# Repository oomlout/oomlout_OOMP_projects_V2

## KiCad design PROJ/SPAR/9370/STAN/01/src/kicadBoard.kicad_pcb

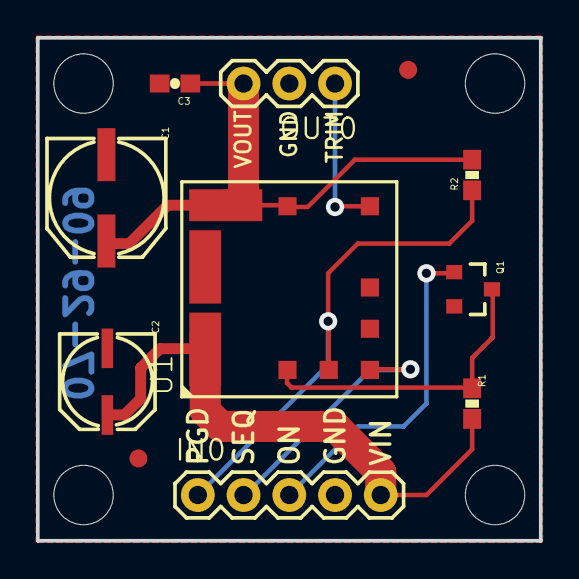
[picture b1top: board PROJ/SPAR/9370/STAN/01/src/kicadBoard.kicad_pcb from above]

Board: 16 copper layers, 27.9 x 27.9 mm, 16 parts (1 on the bottom side), 8 nets.

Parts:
C1: 100uF-25V; NIPPON_F80
C2: 22uF-35v; PANASONIC_C
C3: 0.1uF; 0603-CAP
FID1, FID2: FIDUCIAL1X2; FIDUCIAL-1X2
IN0: 1X05
OUT0: 1X03
Q1: MOSFET-NCHANNELSMD; SOT23-3
R1: 22K; 0603-RES
R2: 100K; 0603-RES
U1: DC-DC_CONVERTER
U$1, U$3, U$4, U$5: STAND-OFF
U$2: LOGO-SFENEW; SFE-NEW-WEBLOGO

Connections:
GND: C1.-, C2.-, C3.2, IN0.4, OUT0.2, Q1.2, U1.3, U1.7
unnamed: Q1.3, R1.1, U1.1
ON/OFF: IN0.3, Q1.1
PGOOD: IN0.1, R2.1, U1.10
SEQ: IN0.2, U1.9
TRIM: OUT0.1, U1.6
VIN: C2.+, IN0.5, R1.2, U1.2
VOUT: C1.+, C3.1, OUT0.3, R2.2, U1.4, U1.5

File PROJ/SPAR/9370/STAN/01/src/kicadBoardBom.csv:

"Id";"Designator";"Package";"Quantity";"Designation";"Supplier and ref";
1;"C3";"0603-CAP";1;"0.1uF";;;
2;"U$3,U$5,U$1,U$4";"STAND-OFF";4;"STAND-OFF";;;
3;"Q1";"SOT23-3";1;"MOSFET-NCHANNELSMD";;;
4;"FID2,FID1";"FIDUCIAL-1X2";2;"FIDUCIAL1X2";;;
5;"C1";"NIPPON_F80";1;"100uF-25V";;;
6;"R2";"0603-RES";1;"100K";;;
7;"C2";"PANASONIC_C";1;"22uF-35v";;;
8;"R1";"0603-RES";1;"22K";;;
9;"IN0";"1X05";1;"";;;
10;"U1";"DC-DC_CONVERTER";1;"DC-DC_CONVERTER";;;
11;"OUT0";"1X03";1;"";;;
12;"U$2";"SFE-NEW-WEBLOGO";1;"LOGO-SFENEW";;;

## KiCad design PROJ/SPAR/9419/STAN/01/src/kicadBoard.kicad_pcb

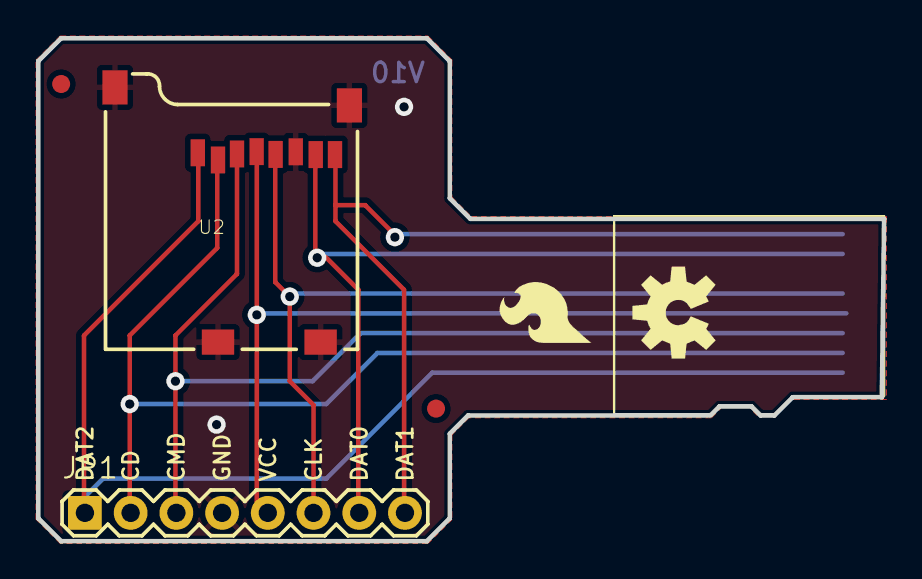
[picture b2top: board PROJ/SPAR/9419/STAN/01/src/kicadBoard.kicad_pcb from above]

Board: 16 copper layers, 47.0 x 27.9 mm, 9 parts (1 on the bottom side), 8 nets.

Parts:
FID1, FID2: FIDUCIAL1X2; FIDUCIAL-1X2
FRAME1: CREATIVE_COMMONS
JP1: 1X08
LOGO1: OSHW-LOGOM; OSHW-LOGO-M
LOGO2: SFE_LOGO_FLAME.2_INCH; SFE_LOGO_FLAME_.2
LOGO3: SFE_LOGO_NAME_FLAME.1_INCH; SFE_LOGO_NAME_FLAME_.1
U1: MICRO-SDCARD
U2: microSD Socket; MICROSD_1_1

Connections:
CD/DAT3: JP1.2, U1.CD/DAT3, U2.2
CLK: JP1.6, U1.CLK, U2.5
CMD: JP1.3, U1.CMD, U2.3
DAT0: JP1.7, U1.DAT0, U2.7
DAT1: JP1.8, U1.DAT1, U2.8
DAT2: JP1.1, U1.DAT2, U2.1
GND: JP1.4, U1.GND, U2.6, U2.CD1, U2.CD2, U2.GND1, U2.GND3
VCC: JP1.5, U1.VCC, U2.4

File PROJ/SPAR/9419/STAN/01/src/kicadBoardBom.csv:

"Id";"Designator";"Package";"Quantity";"Designation";"Supplier and ref";
1;"FID1,FID2";"FIDUCIAL-1X2";2;"FIDUCIAL1X2";;;
2;"U1";"MICRO-SDCARD";1;"MICRO-SDCARD";;;
3;"JP1";"1X08";1;"";;;
4;"LOGO1";"OSHW-LOGO-M";1;"OSHW-LOGOM";;;
5;"U2";"MICROSD_1_1";1;"microSD Socket";;;
6;"LOGO2";"SFE_LOGO_FLAME_.2";1;"SFE_LOGO_FLAME.2_INCH";;;
7;"FRAME1";"CREATIVE_COMMONS";1;"";;;
8;"LOGO3";"SFE_LOGO_NAME_FLAME_.1";1;"SFE_LOGO_NAME_FLAME.1_INCH";;;

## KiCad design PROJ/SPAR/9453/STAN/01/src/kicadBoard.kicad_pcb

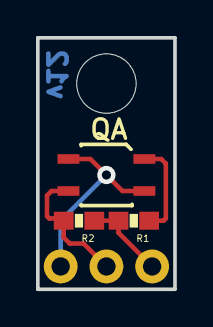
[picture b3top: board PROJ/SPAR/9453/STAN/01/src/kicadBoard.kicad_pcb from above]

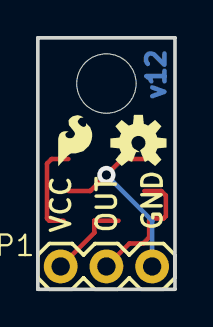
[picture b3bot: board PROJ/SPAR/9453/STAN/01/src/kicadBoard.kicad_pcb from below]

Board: 2 copper layers, 7.6 x 14.0 mm, 8 parts (3 on the bottom side), 4 nets.

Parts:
CC_TEXT1: CREATIVE_COMMONS
JP1: 1X03
JP2: LOGO-SFESK; SFE-LOGO-FLAME
JP3: STAND-OFF
R1: 100; 0603-RES
R2: 10K; 0603-RES
U1: QRE11131:1; QRE1113-1_1
U$1: OSHW-LOGOS; OSHW-LOGO-S

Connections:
GND: JP1.3, U1.2, U1.4
unnamed: R1.1, U1.1
OUT: JP1.2, R2.2, U1.3
VCC: JP1.1, R1.2, R2.1

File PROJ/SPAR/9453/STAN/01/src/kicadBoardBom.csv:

"Id";"Designator";"Package";"Quantity";"Designation";"Supplier and ref";
1;"U1";"QRE1113-1_1";1;"QRE11131:1";;;
2;"JP3";"STAND-OFF";1;"STAND-OFF";;;
3;"CC_TEXT1";"CREATIVE_COMMONS";1;"CREATIVE_COMMONS";;;
4;"R1";"0603-RES";1;"100";;;
5;"R2";"0603-RES";1;"10K";;;
6;"JP2";"SFE-LOGO-FLAME";1;"LOGO-SFESK";;;
7;"U$1";"OSHW-LOGO-S";1;"OSHW-LOGOS";;;
8;"JP1";"1X03";1;"";;;

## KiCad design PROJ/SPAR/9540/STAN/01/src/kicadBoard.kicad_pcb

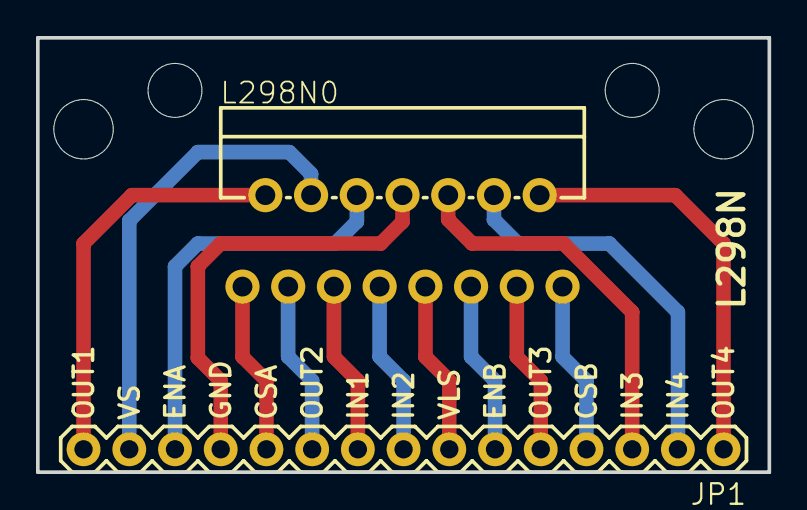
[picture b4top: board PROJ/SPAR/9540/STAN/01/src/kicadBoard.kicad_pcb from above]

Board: 2 copper layers, 40.6 x 24.1 mm, 5 parts (1 on the bottom side), 15 nets.

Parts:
JP1: M15; 1X15
JP2, JP3: STAND-OFF
JP4: LOGO-SFENEW; SFE-NEW-WEBLOGO
L298N0: L298HEATSINK; MULTIWATT15_6400BGHEATSINK

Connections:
CSA: JP1.11, L298N0.1
CSB: JP1.4, L298N0.15
ENA: JP1.13, L298N0.6
ENB: JP1.6, L298N0.11
GND: JP1.12, L298N0.8
IN1: JP1.9, L298N0.5
IN2: JP1.8, L298N0.7
IN3: JP1.3, L298N0.10
IN4: JP1.2, L298N0.12
OUT1: JP1.15, L298N0.2
OUT2: JP1.10, L298N0.3
OUT3: JP1.5, L298N0.13
OUT4: JP1.1, L298N0.14
VLS: JP1.7, L298N0.9
VS: JP1.14, L298N0.4

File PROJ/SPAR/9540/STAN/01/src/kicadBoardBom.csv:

"Id";"Designator";"Package";"Quantity";"Designation";"Supplier and ref";
1;"L298N0";"MULTIWATT15_6400BGHEATSINK";1;"L298HEATSINK";;;
2;"JP1";"1X15";1;"M15";;;
3;"JP2,JP3";"STAND-OFF";2;"STAND-OFF";;;
4;"JP4";"SFE-NEW-WEBLOGO";1;"LOGO-SFENEW";;;

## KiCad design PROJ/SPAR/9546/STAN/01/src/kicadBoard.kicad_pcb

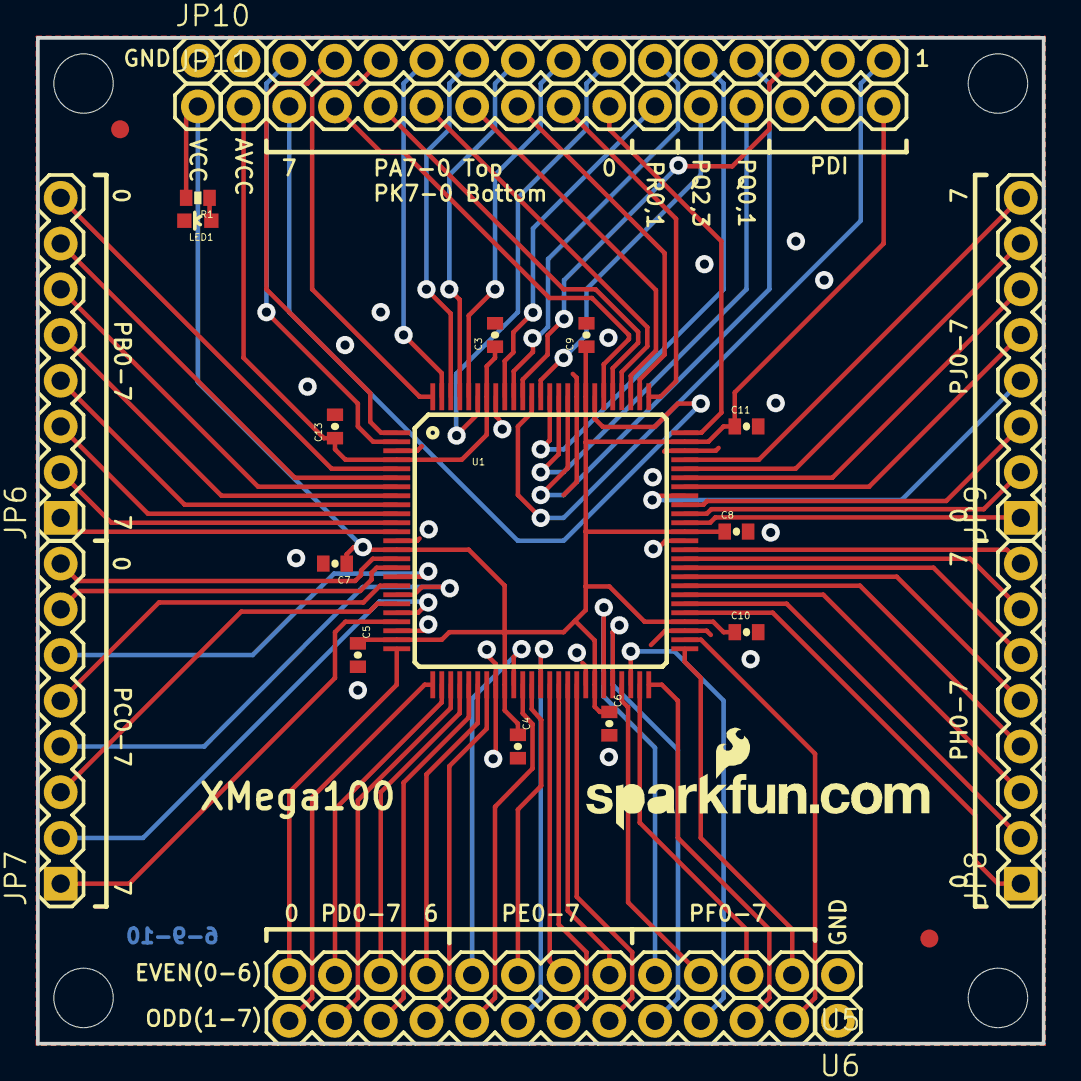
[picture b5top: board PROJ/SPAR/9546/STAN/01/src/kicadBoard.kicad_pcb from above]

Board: 2 copper layers, 55.9 x 55.9 mm, 28 parts (0 on the bottom side), 84 nets.

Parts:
C3, C4, C5, C6, C7, C8, C9, C10, C11, C13: 0.1uF; 0402-CAP
JP1: LOGO-SFENEW; SFE-NEW-WEBLOGO
JP2, JP3, JP4, JP5: STAND-OFF
JP6: Left Port B; 1X08
JP7: Left Port C; 1X08
JP8: Right Port H; 1X08
JP9: Right Port J; 1X08
JP10: TopEdge; 1X16
JP11: TopInside; 1X16
JP12, JP13: FIDUCIAL1X2; FIDUCIAL-1X2
LED1: Red; LED-0603
R1: 330; 0402-RES
U1: XMEGA-100SMD; TQFP-100-14X14MM
U5: BottonInside; 1X13
U6: BottomEdge; 1X13

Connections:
AVCC: C3.1, C13.1, JP11.2, U1.4, U1.94
GND: C3.2, C4.2, C5.2, C6.2, C7.2, C8.2, C9.2, C10.2, C11.2, C13.2, JP10.1, JP10.2, JP11.14, LED1.C, U1.3, U1.13, U1.23, U1.33, U1.43, U1.53, U1.63, U1.73, U1.84, U1.93, U5.1, U6.1
unnamed: LED1.A, R1.1
PA0: JP10.10, U1.95
PA1: JP10.9, U1.96
PA2: JP10.8, U1.97
PA3: JP10.7, U1.98
PA4: JP10.6, U1.99
PA5: JP10.5, U1.100
PA6: JP10.4, U1.1
PA7: JP10.3, U1.2
PB0: JP6.8, U1.5
PB1: JP6.7, U1.6
PB2: JP6.6, U1.7
PB3: JP6.5, U1.8
PB4: JP6.4, U1.9
PB5: JP6.3, U1.10
PB6: JP6.2, U1.11
PB7: JP6.1, U1.12
PC0: JP7.8, U1.15
PC1: JP7.7, U1.16
PC2: JP7.6, U1.17
PC3: JP7.5, U1.18
PC4: JP7.4, U1.19
PC5: JP7.3, U1.20
PC6: JP7.2, U1.21
PC7: JP7.1, U1.22
PD0: U1.25, U5.13
PD1: U1.26, U6.13
PD2: U1.27, U5.12
PD3: U1.28, U6.12
PD4: U1.29, U5.11
PD5: U1.30, U6.11
PD6: U1.31, U5.10
PD7: U1.32, U6.10
PDI_CLK: JP10.14, U1.90
PDI_DATA: JP10.16, U1.89
PE0: U1.35, U5.9
PE1: U1.36, U6.9
PE2: U1.37, U5.8
PE3: U1.38, U6.8
PE4: U1.39, U5.7
PE5: U1.40, U6.7
PE6: U1.41, U5.6
PE7: U1.42, U6.6
PF0: U1.45, U5.5
PF1: U1.46, U6.5
PF2: U1.47, U5.4
PF3: U1.48, U6.4
PF4: U1.49, U5.3
PF5: U1.50, U6.3
PF6: U1.51, U5.2
PF7: U1.52, U6.2
PH0: JP8.1, U1.55
PH1: JP8.2, U1.56
PH2: JP8.3, U1.57
PH3: JP8.4, U1.58
PH4: JP8.5, U1.59
PH5: JP8.6, U1.60
PH6: JP8.7, U1.61
PH7: JP8.8, U1.62
PJ0: JP9.1, U1.65
PJ1: JP9.2, U1.66
PJ2: JP9.3, U1.67
PJ3: JP9.4, U1.68
PJ4: JP9.5, U1.69
PJ5: JP9.6, U1.70
PJ6: JP9.7, U1.71
PJ7: JP9.8, U1.72
PK0: JP11.10, U1.75
PK1: JP11.9, U1.76
PK2: JP11.8, U1.77
PK3: JP11.7, U1.78
PK4: JP11.6, U1.79
PK5: JP11.5, U1.80
PK6: JP11.4, U1.81
PK7: JP11.3, U1.82
PQ0: JP10.13, U1.85
PQ1: JP11.13, U1.86
PQ2: JP10.12, U1.87
PQ3: JP11.12, U1.88
PR0: JP10.11, U1.91
PR1: JP11.11, U1.92
VCC: C4.1, C5.1, C6.1, C7.1, C8.1, C9.1, C10.1, C11.1, JP11.1, JP11.16, R1.2, U1.14, U1.24, U1.34, U1.44, U1.54, U1.64, U1.74, U1.83

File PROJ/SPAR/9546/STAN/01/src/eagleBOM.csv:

"Part";"Value";"Device";"Package";"Description";"";
"C3";"0.1uF";"CAP0402-CAP";"0402-CAP";"Capacitor";"";
"C4";"0.1uF";"CAP0402-CAP";"0402-CAP";"Capacitor";"";
"C5";"0.1uF";"CAP0402-CAP";"0402-CAP";"Capacitor";"";
"C6";"0.1uF";"CAP0402-CAP";"0402-CAP";"Capacitor";"";
"C7";"0.1uF";"CAP0402-CAP";"0402-CAP";"Capacitor";"";
"C8";"0.1uF";"CAP0402-CAP";"0402-CAP";"Capacitor";"";
"C9";"0.1uF";"CAP0402-CAP";"0402-CAP";"Capacitor";"";
"C10";"0.1uF";"CAP0402-CAP";"0402-CAP";"Capacitor";"";
"C11";"0.1uF";"CAP0402-CAP";"0402-CAP";"Capacitor";"";
"C13";"0.1uF";"CAP0402-CAP";"0402-CAP";"Capacitor";"";
"JP1";"LOGO-SFENEW";"LOGO-SFENEW";"SFE-NEW-WEBLOGO";"Spark Fun Electronics PCB Logo";"";
"JP2";"STAND-OFF";"STAND-OFF";"STAND-OFF";"Stand Off";"";
"JP3";"STAND-OFF";"STAND-OFF";"STAND-OFF";"Stand Off";"";
"JP4";"STAND-OFF";"STAND-OFF";"STAND-OFF";"Stand Off";"";
"JP5";"STAND-OFF";"STAND-OFF";"STAND-OFF";"Stand Off";"";
"JP6";"Left Port B";"M08";"1X08";"Header 8";"";
"JP7";"Left Port C";"M08";"1X08";"Header 8";"";
"JP8";"Right Port H";"M08";"1X08";"Header 8";"";
"JP9";"Right Port J";"M08";"1X08";"Header 8";"";
"JP10";"TopEdge";"M16PTH";"1X16";"";"";
"JP11";"TopInside";"M16PTH";"1X16";"";"";
"JP12";"FIDUCIAL1X2";"FIDUCIAL1X2";"FIDUCIAL-1X2";"Fiducial Alignment Points";"";
"JP13";"FIDUCIAL1X2";"FIDUCIAL1X2";"FIDUCIAL-1X2";"Fiducial Alignment Points";"";
"LED1";"Red";"LED0603";"LED-0603";"LEDs";"";
"R1";"330";"RESISTOR0402-RES";"0402-RES";"Resistor";"";
"U1";"XMEGA-100SMD";"XMEGA-100SMD";"TQFP-100-14X14MM";"";"";
"U5";"BottonInside";"M13";"1X13";"";"";
"U6";"BottomEdge";"M13";"1X13";"";"";

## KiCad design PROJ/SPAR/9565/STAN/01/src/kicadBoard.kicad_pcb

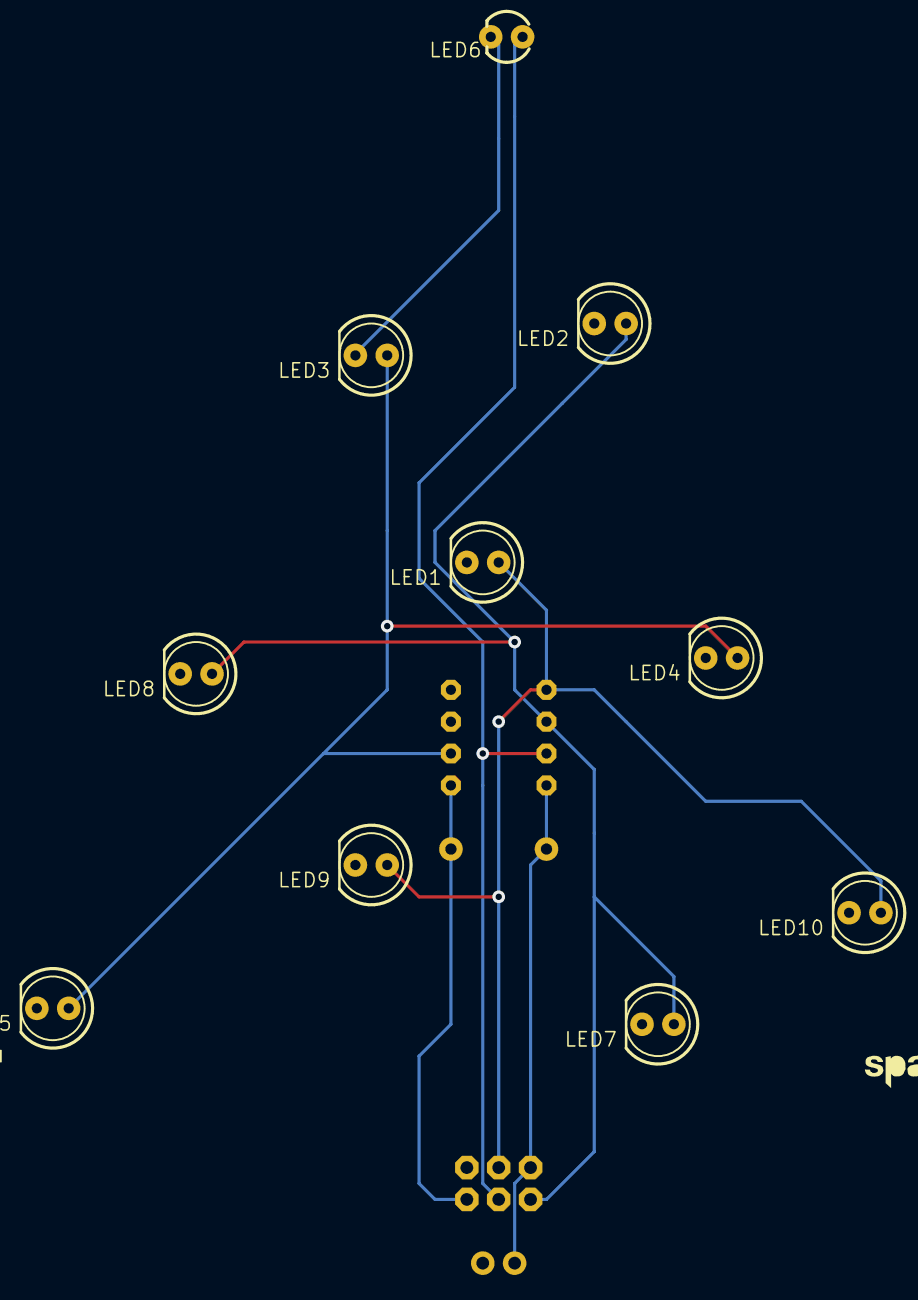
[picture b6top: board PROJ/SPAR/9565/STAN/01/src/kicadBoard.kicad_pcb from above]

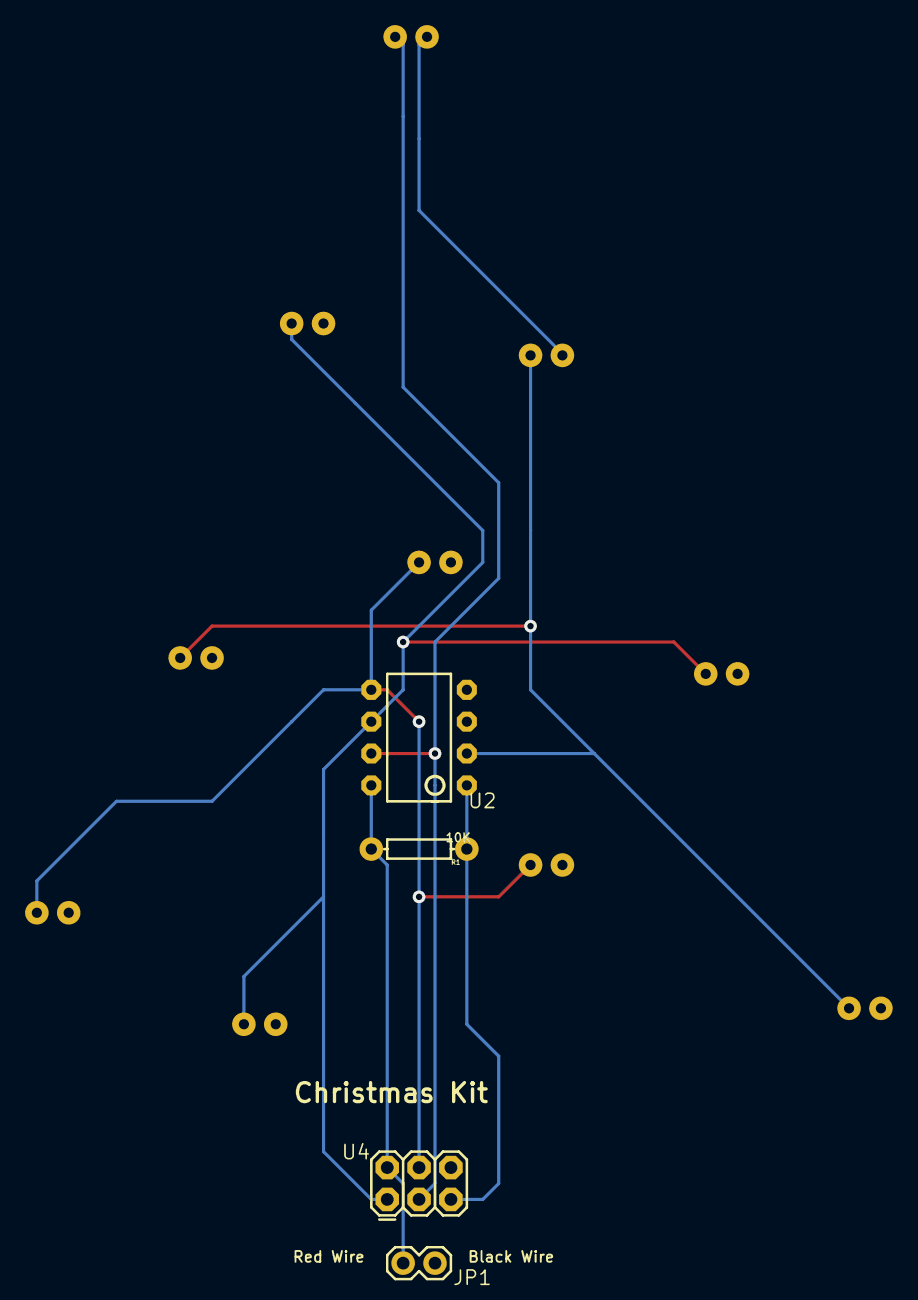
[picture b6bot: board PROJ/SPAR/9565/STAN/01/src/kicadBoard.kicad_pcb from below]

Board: 2 copper layers, 19 parts (4 on the bottom side), 7 nets.

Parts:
@HOLE0: (no value)
FRAME1: FRAME-LETTER; CREATIVE_COMMONS
JP1: 1X02
JP2: LOGO-SFENEW; SFE-NEW-WEBLOGO
LED1, LED2, LED3, LED4, LED5, LED7, LED8, LED9, LED10: GREEN; LED5MM
LED6: YELLOW; LED3MM
LOGO1: OSHW-LOGOL; OSHW-LOGO-L
R1: 10K; AXIAL-0.3
U2: ATTINY13DIP; DIP08
U4: AVR_SPI_PRG_6PTH; 2X3
U$1: REVISION

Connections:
GND: JP1.1, LED1.K, LED2.K, LED3.K, LED4.K, LED5.K, LED6.K, LED7.K, LED8.K, LED9.K, LED10.K, U2.4, U4.6
LED1: LED1.A, LED9.A, LED10.A, U2.5, U4.4
LED2: LED2.A, LED7.A, LED8.A, U2.6, U4.1
LED3: LED3.A, LED4.A, LED5.A, U2.2
RESET: R1.P$1, U2.1, U4.5
SCK: LED6.A, U2.7, U4.3
VCC: JP1.2, R1.P$2, U2.8, U4.2

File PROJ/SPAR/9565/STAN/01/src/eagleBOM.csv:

"Part";"Value";"Device";"Package";"Description";"";
"FRAME1";"FRAME-LETTER";"FRAME-LETTER";"CREATIVE_COMMONS";"Schematic Frame";"";
"JP1";"";"M02PTH";"1X02";"Header 2";"";
"JP2";"LOGO-SFENEW";"LOGO-SFENEW";"SFE-NEW-WEBLOGO";"Spark Fun Electronics PCB Logo";"";
"LED1";"GREEN";"LED5MM";"LED5MM";"LEDs";"";
"LED2";"GREEN";"LED5MM";"LED5MM";"LEDs";"";
"LED3";"GREEN";"LED5MM";"LED5MM";"LEDs";"";
"LED4";"GREEN";"LED5MM";"LED5MM";"LEDs";"";
"LED5";"GREEN";"LED5MM";"LED5MM";"LEDs";"";
"LED6";"YELLOW";"LED3MM";"LED3MM";"LEDs";"";
"LED7";"GREEN";"LED5MM";"LED5MM";"LEDs";"";
"LED8";"GREEN";"LED5MM";"LED5MM";"LEDs";"";
"LED9";"GREEN";"LED5MM";"LED5MM";"LEDs";"";
"LED10";"GREEN";"LED5MM";"LED5MM";"LEDs";"";
"LOGO1";"OSHW-LOGOL";"OSHW-LOGOL";"OSHW-LOGO-L";"Open Source Hardware Logo This logo indicates the piece of hardware it is found on incorporates a OSHW license and/or adheres to the definition of open source hardware found here: http://freedomdefined.org/OSHW";"";
"R1";"10K";"RESISTORPTH1";"AXIAL-0.3";"Resistor";"";
"U$1";"REVISION";"REVISION";"REVISION";"";"";
"U2";"ATTINY13DIP";"ATTINY13DIP";"DIP08";"";"";
"U4";"AVR_SPI_PRG_6PTH";"AVR_SPI_PRG_6PTH";"2X3";"AVR ISP 6 Pin";"";

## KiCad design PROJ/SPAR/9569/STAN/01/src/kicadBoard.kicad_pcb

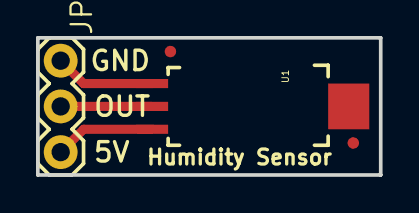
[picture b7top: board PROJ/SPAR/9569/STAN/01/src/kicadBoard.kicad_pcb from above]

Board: 2 copper layers, 19.1 x 7.6 mm, 5 parts (1 on the bottom side), 3 nets.

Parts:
FID1, FID2: FIDUCIALUFIDUCIAL; MICRO-FIDUCIAL
JP1: 1X03
JP2: LOGO-SFESK; SFE-LOGO-FLAME
U1: HIH-4030SMD; HIH-4030

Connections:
GND: JP1.1, U1.1
OUT: JP1.2, U1.2
VCC: JP1.3, U1.3

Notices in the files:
parts and their libraries:
RELEASED UNDER THE CREATIVE COMMONS ATTRIBUTION SHARE-ALIKE 4.0 LICENSE
HTTPS://CREATIVECOMMONS.ORG/LICENSES/BY-SA/4.0
HTTP://CREATIVECOMMONS.ORG/LICENSES/BY-SA/3.0
RELEASED UNDER THE CREATIVE COMMONS ATTRIBUTION SHARE-ALIKE 3.0 LICENSE
